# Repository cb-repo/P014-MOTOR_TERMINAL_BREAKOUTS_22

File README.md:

# 22mm MOTOR TERMINAL BREAKOUT v1.1 (2-pack)

Motor terminals are traditionally small and flimsy, making it hard to guarantee a reliable solder connection.
MOTOR TERMINAL BREAKOUTS are designed to simplify and strengthen these solder joints, enabling more reliable operation especally in high vibration environments: orignially designed for combat robotics but is suitable for any application using these motors. 
  
Developed, assembled, and tested in [Christchurch, New Zealand](https://www.google.co.nz/maps/place/Christchurch+New+Zealand), by Connor Benton.

## FEATURES
- Mounts to the motor at 0°, 45°, 90°, and 135° angles
- Large solder pads enable stronger connections to the wires
- Pads are broken out onto PCB 'fingers' allowing the wires to be individually heatshrunk (providing even greater mechanical strength)
- Capacitor across the motor output to filter noise and voltage spikes

## SPECIFICATIONS
- **Dimensions:** 20x25.5x2.4 mm
- **Weight:** 1g each
- **Capacitance:** 100nF
- **Material:** Fiberglass

## PACKAGE INCLUDES

- 2x 22mm MOTOR TERMINAL BREAKOUTS

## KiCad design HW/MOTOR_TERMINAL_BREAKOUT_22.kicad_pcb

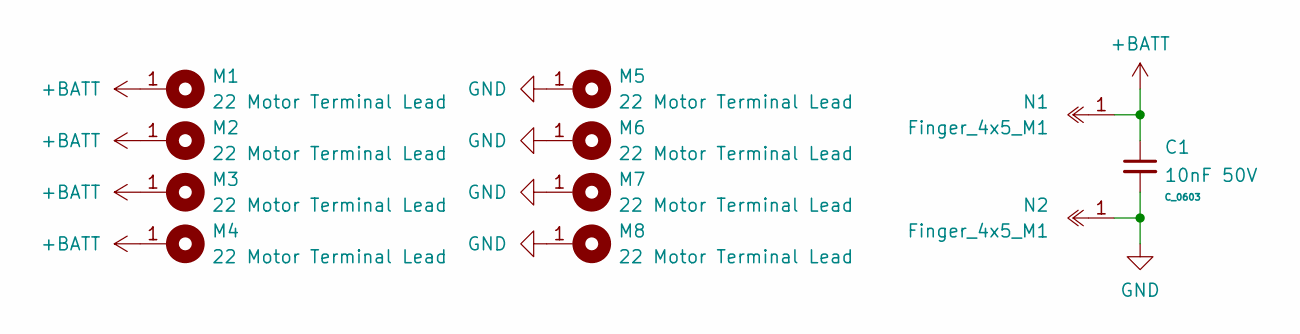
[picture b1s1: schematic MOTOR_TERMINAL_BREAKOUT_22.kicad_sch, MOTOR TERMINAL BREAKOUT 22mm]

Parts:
C1: 10nF 50V; C_0603; MFG Part CC0603KRX7R9BB103; LCSC_Part C100042
M1, M2, M3, M4, M5, M6, M7, M8: 22 Motor Terminal Lead
N1, N2: Finger_4x5_M1

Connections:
+BATT: C1.1, M1.1, M2.1, M3.1, M4.1, N1.1
GND: C1.2, M5.1, M6.1, M7.1, M8.1, N2.1

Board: 2 copper layers, 11 parts (0 on the bottom side), 2 nets, no tracks yet.

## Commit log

2022-07-19 Initialise LFS in Repo
2022-07-31 Generate First Revision of Breakout for 22mm Motor
2022-07-31 Update Silkscreen to Add Revision Number
2022-07-31 Remove Backups from Repo
2022-08-09 Update README for release to CRNZ
2024-04-17 Update design to v1.1 for next manufacturing run
2024-06-04 Fix Product Label Bug
2025-09-10 Update Production Files and Manufacture Label
2025-09-16 Create v1.0 Datasheet
2025-09-16 Update Datasheet with Package Includes Section
2025-09-16 Retroactively Update v1.0 Datasheet
2025-09-16 Update Datasheet for v1.1 Hardware
